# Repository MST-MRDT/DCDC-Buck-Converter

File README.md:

# DCDC-Buck-Converter
Repo for the hardware files for the DC/DC buck converter

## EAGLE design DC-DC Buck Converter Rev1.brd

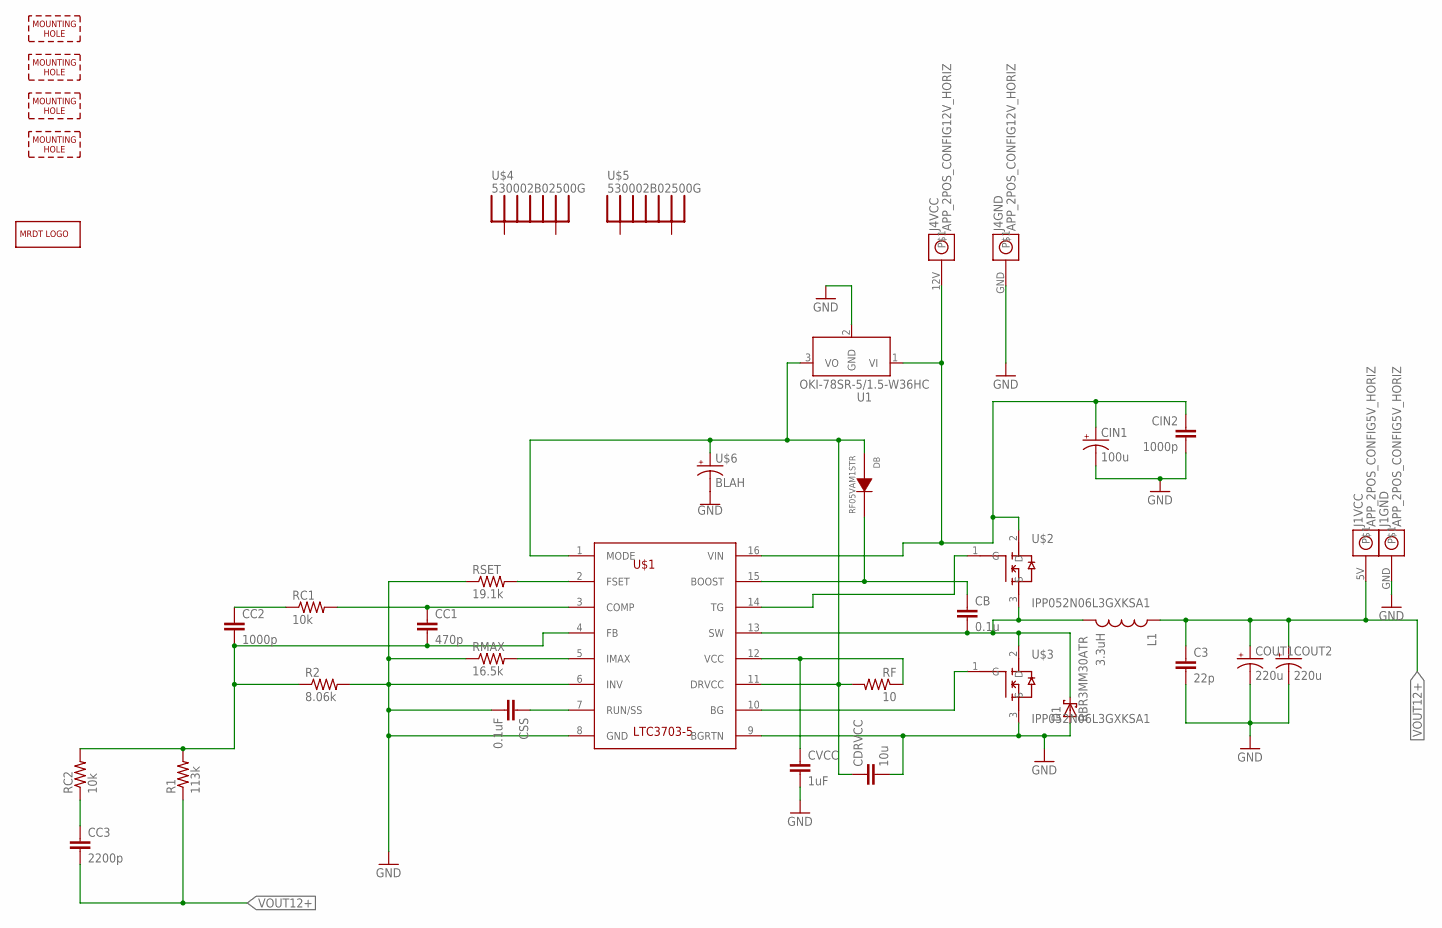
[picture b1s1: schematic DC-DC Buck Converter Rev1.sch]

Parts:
C3: 22p; 0603-CAP
CB: 0.1u; 0603-CAP
CC1: 470p; 0603-CAP
CC2: 1000p; 0603-CAP
CC3: 2200p; 0603-CAP
CDRVCC: 10u; 0603-CAP
CIN1: 100u; CAP_POL_220UF
CIN2: 1000p; 0603-CAP
COUT1, COUT2: 220u; CAP_POL_220UF
CSS: 0.1uF; 0603-CAP
CVCC: 1uF; 0603-CAP
D1: RBR3MM30ATR; DIODE_SCHOTTKY_30V_1A
DB: RF05VAM1STR; DIODE_STANDARD_100V
H1, H2, H3, H4: MOUNTING_HOLE#8; #8_SCREW
J1: APP_2POS_CONFIG5V_HORIZ; APP45_5V_HORIZ_CONFIG
J4: APP_2POS_CONFIG12V_HORIZ; APP45_12V_HORIZ_CONFIG
L1: 3.3uH; PLANAR_INDUCTOR_3.3UH
LOGO1: MRDT_LOGO
R1: 113k; 0603-RES
R2: 8.06k; 0603-RES
RC1, RC2: 10k; 0603-RES
RF: 10; 0603-RES
RMAX: 16.5k; 0603-RES
RSET: 19.1k; 0603-RES
U1: OKI-78SR-5/1.5-W36HC; OKI-78SR_HORIZ
U$1: LTC3703-5; SSOP-16
U$2, U$3: IPP052N06L3GXKSA1; TO-220
U$4, U$5: 530002B02500G; RADIAL_FIN_HEATSINK
U$6: BLAH

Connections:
5V: CDRVCC.1, DB.P$2 (A), RF.2, U1.3 (VO), U$1.1 (MODE), U$1.11 (DRVCC), U$6.P$2 (+)
GND: C3.2, CDRVCC.2, CIN1.GND (-), CIN2.2, COUT1.GND (-), COUT2.GND (-), CSS.2, CVCC.2, D1.P$1 (A), J1.GND, J4.GND, R2.2, RMAX.1, RSET.1, U1.2 (GND), U$1.6 (INV), U$1.8 (GND), U$1.9 (BGRTN), U$3.3 (S), U$6.P$1 (-)
unnamed: CB.1, DB.P$1 (K), U$1.15 (BOOST)
unnamed: U$1.14 (TG), U$2.1 (G)
unnamed: RSET.2, U$1.2 (FSET)
unnamed: RMAX.2, U$1.5 (IMAX)
unnamed: CSS.1, U$1.7 (RUN/SS)
unnamed: CC1.1, RC1.2, U$1.3 (COMP)
unnamed: CC2.1, RC1.1
unnamed: CC3.1, RC2.1
unnamed: CC1.2, CC2.2, R1.2, R2.1, RC2.2, U$1.4 (FB)
unnamed: CVCC.1, RF.1, U$1.12 (VCC)
unnamed: U$1.10 (BG), U$3.1 (G)
unnamed: CB.2, D1.P$2 (C), L1.P$2 (2), U$1.13 (SW), U$2.3 (S), U$3.2 (D)
VBATT: CIN1.+, CIN2.1, J4.12V, U1.1 (VI), U$1.16 (VIN), U$2.2 (D)
VOUT12+: C3.1, CC3.2, COUT1.+, COUT2.+, J1.5V, L1.P$1 (1), R1.1

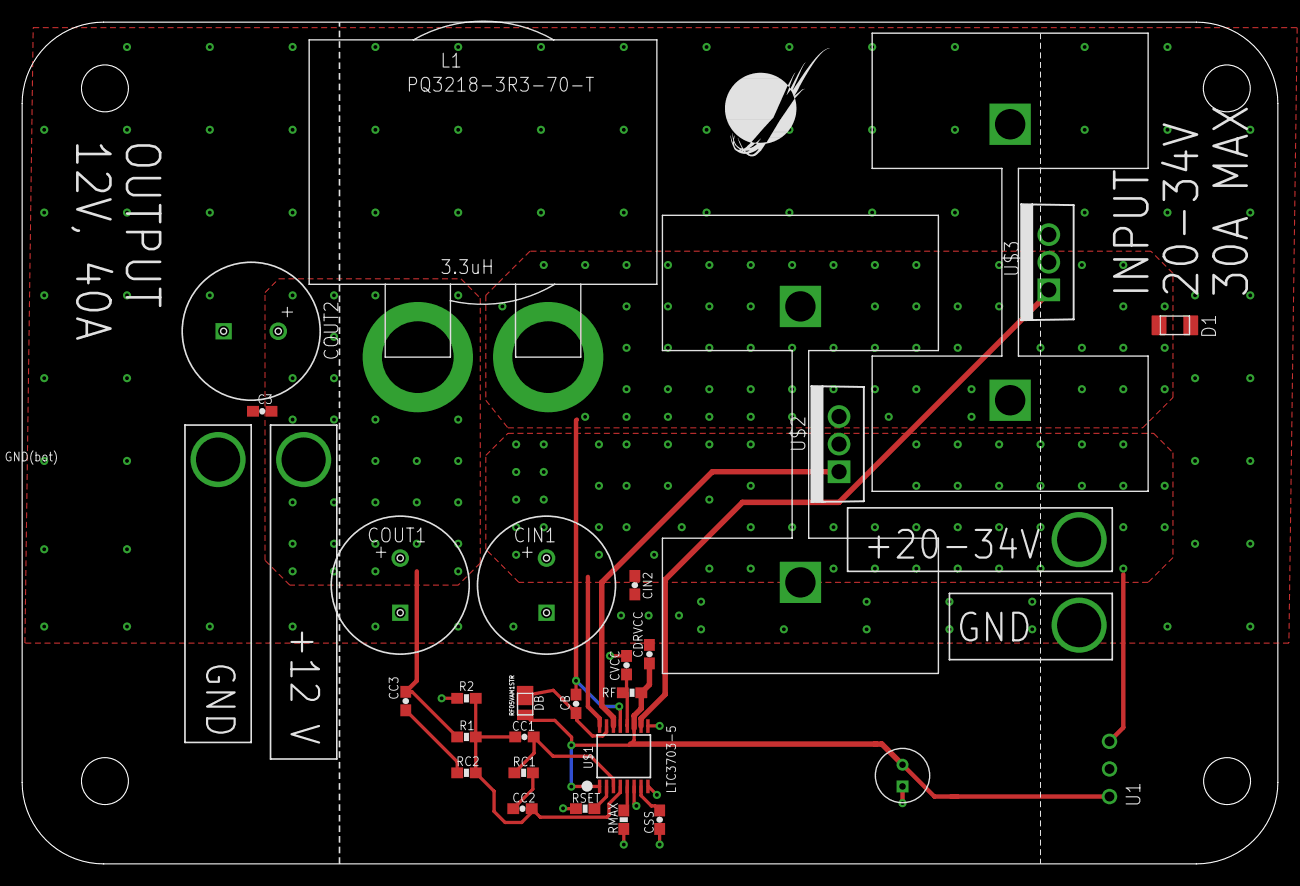
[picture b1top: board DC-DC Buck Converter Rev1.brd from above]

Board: 2 copper layers, 115.6 x 77.5 mm, 36 parts (0 on the bottom side), 16 nets.

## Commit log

2017-10-12 Initial Schematic
    Need to replace dummy components with real components with actual footprint
2017-10-14 Updated a few components
    COUT 1, COUT 2, CIN1, and C1 now correspond to their true package
2017-10-14 Updated with all real components
    Added devices for inductor, diodes, and mosfets
2017-10-14 Board design initiated
2017-10-15 Revision 1 routing complete
    LTC3703-5 datasheet provided a list of constraints that had to be worked around. Ground plane separated into a signal ground and a power ground. Some components needed to be placed close to the IC as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
2017-10-15 Major rearrangements
2017-10-16 Reconfigured board, still doesn't support 40A
2017-10-23 New layout, do power power path
2017-10-24 Routing completed, needs to be approved
    Added complete via stitching around all power traces. Signal ground in lower right joined to power ground close to negative output terminal. Sloppy routing under LTC chip, could be cleaner probably
2017-10-25 Major revision, moved LTC to bottom
    Changed signal traces to be much closer to LTC chip. Modified via stitching to cover whole polygon rather than edges only. No more vias under IC. Moved inductor to top side of board to prevent LTC fr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
2017-10-26 Finishing touches
    Finished via stitching, added labels and logo, adjusted mounting holes
2017-10-28 Switched to upright mosfets, adjusted board accordingly
    Spread out some of the signal components on the bottom side of the board. Adjusted power planes to compensate for new mosfet orientation.
2017-10-29 Improved silkscreen labeling
    Moved labeling to tplace layer because tsilk layer does not pront in manufacturing. Elarged labels on each resistor and capacitor to help in populating the board.
2017-10-30 Heatsinks added, rearranges needed
2017-10-30 Power traces turned horizontal
2017-11-02 Final revision for testing
    Finished via stitching
2017-11-02 Rev1 Gerb Files and Folder Cleanup
    Changed names of files from switching regulator to DC-DC Buck Converter. Zipped folder containing the Gerb files for ordering Rev1 added. Added gitignore that will hopefully work since some unwanted 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
2017-12-03 Add Simulation
2018-02-13 Small changes
    Replaced Oki capacitor, moved diode, deleted output anderson

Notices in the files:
parts and their libraries:
SparkFun-Passives: Licensing: Creative Commons ShareAlike 4.0 International - https://creativecommons.org/licenses/by-sa/4.0
